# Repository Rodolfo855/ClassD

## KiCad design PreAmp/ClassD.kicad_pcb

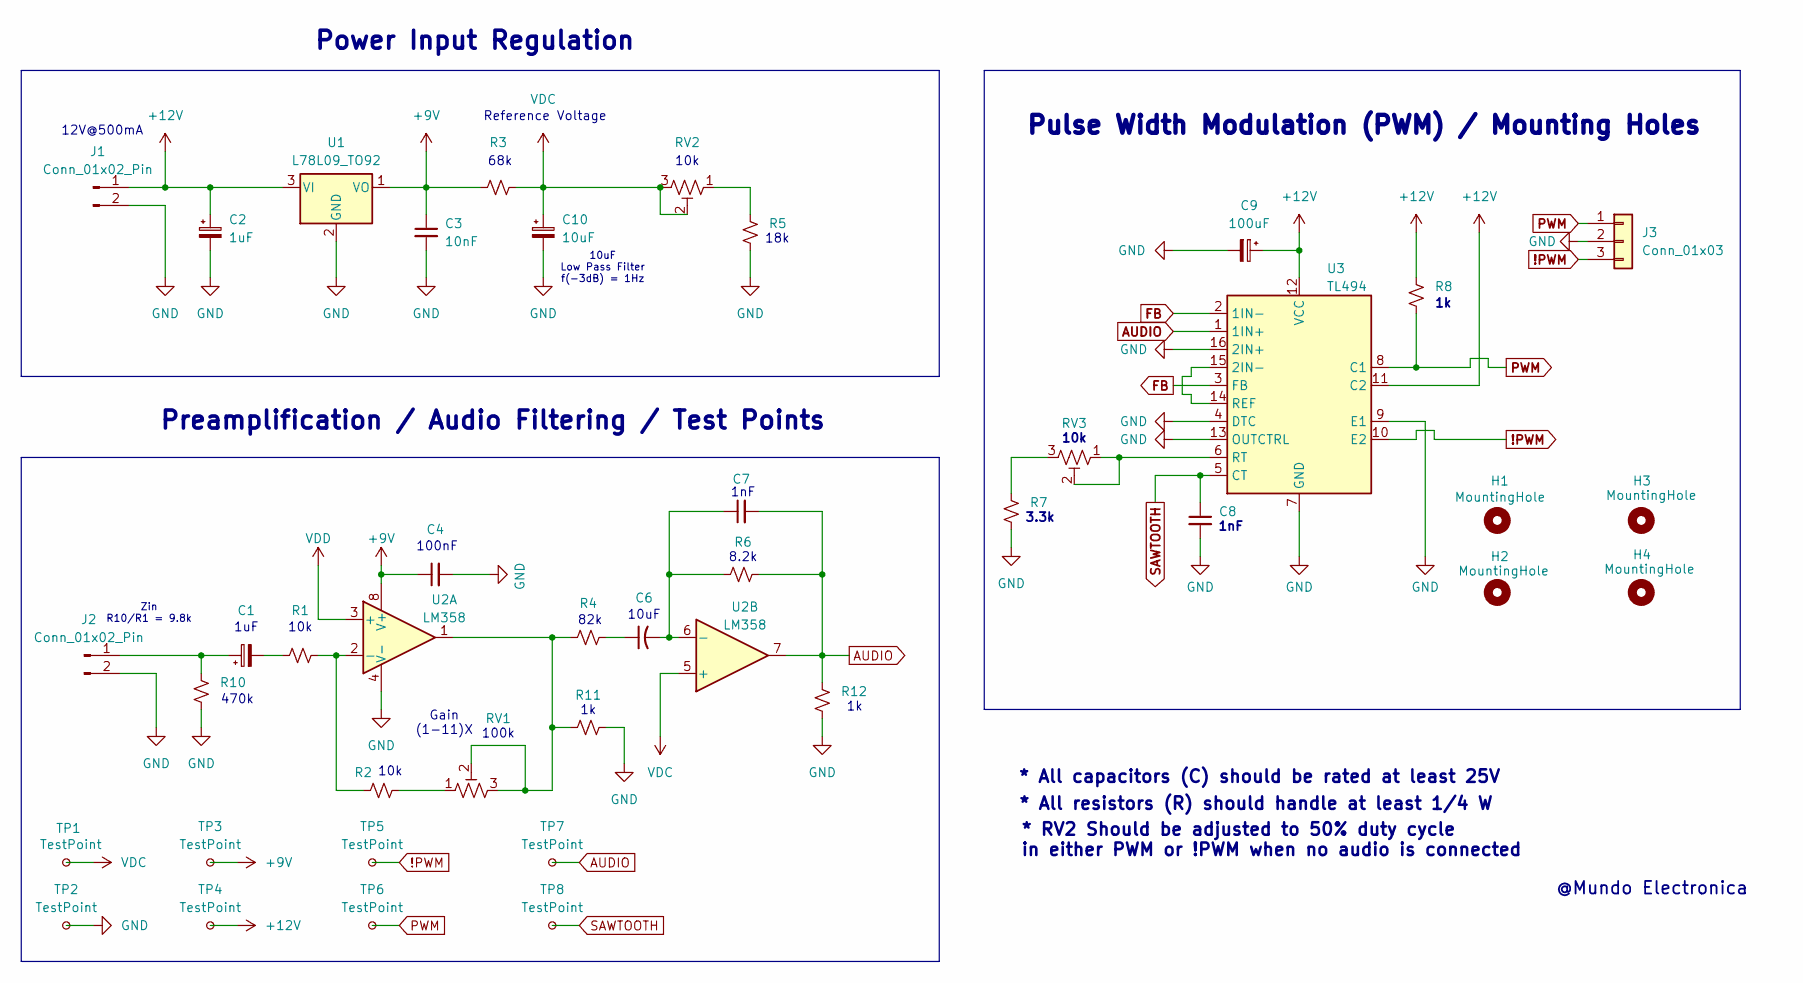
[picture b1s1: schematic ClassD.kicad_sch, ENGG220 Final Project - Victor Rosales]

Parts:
C1: C_Polarized_Small; CP_Radial_D5.0mm_P2.00mm
C2: 1uF; CP_Radial_D5.0mm_P2.00mm
C3: 10nF; C_Disc_D3.8mm_W2.6mm_P2.50mm
C4: C_Small; C_Disc_D5.0mm_W2.5mm_P5.00mm
C6: C_Small_US; CP_Radial_D5.0mm_P2.00mm
C7, C8: C_Small; C_Disc_D3.8mm_W2.6mm_P2.50mm
C9: 100uF; CP_Radial_D8.0mm_P3.50mm
C10: 10uF; CP_Radial_D5.0mm_P2.00mm
H1, H2, H3, H4: MountingHole; MountingHole_3.2mm_M3_Pad_Via
J1: Conn_01x02_Pin; BarrelJack_GCT_DCJ200-10-A_Horizontal
J2: Conn_01x02_Pin; JST_XH_B3B-XH-A_1x03_P2.50mm_Vertical
J3: Conn_01x03; JST_XH_B3B-XH-A_1x03_P2.50mm_Vertical
R1, R2, R3, R4, R5, R6, R7, R8, R10, R11, R12: R_Small_US; R_Axial_DIN0204_L3.6mm_D1.6mm_P7.62mm_Horizontal
RV1, RV2, RV3: R_Potentiometer_Trim_US; Potentiometer_Bourns_3296W_Vertical
TP1, TP2, TP3, TP4, TP5, TP6, TP7, TP8: TestPoint; TestPoint_THTPad_D2.0mm_Drill1.0mm
U1: L78L09_TO92; TO-92_Inline_Wide
U2: LM358; DIP-8_W7.62mm_Socket
U3: TL494; DIP-18_W7.62mm_Socket

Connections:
!PWM: J3.3, TP5.1, U3.10 (E2)
+9V: C3.1, C4.1, R3.1, TP3.1, U1.1 (VO), U2.8 (V+)
+12V: C2.1, C9.1, J1.1, R8.1, TP4.1, U1.3 (VI), U3.11 (C2), U3.12 (VCC)
AUDIO: C7.2, R6.2, R12.1, TP7.1, U2.7, U3.1 (1IN+)
FB: U3.2 (1IN-), U3.3 (FB)
GND: C2.2, C3.2, C4.2, C8.2, C9.2, C10.2, J1.2, J2.2, J3.2, R5.2, R7.2, R10.2, R11.2, R12.2, TP2.1, U1.2 (GND), U2.4 (V-), U3.4 (DTC), U3.7 (GND), U3.9 (E1), U3.13 (OUTCTRL), U3.16 (2IN+)
unnamed: C1.2, R1.1
unnamed: C6.1, R4.2
unnamed: C1.1, J2.1, R10.1
unnamed: R2.2, RV1.1
unnamed: R5.1, RV2.1
unnamed: R7.1, RV3.3
unnamed: R4.1, R11.1, RV1.2, RV1.3, U2.1
unnamed: R1.2, R2.1, U2.2 (-)
unnamed: C6.2, C7.1, R6.1, U2.6 (-)
unnamed: U3.14 (REF), U3.15 (2IN-)
unnamed: RV3.1, RV3.2, U3.6 (RT)
PWM: J3.1, R8.2, TP6.1, U3.8 (C1)
SAWTOOTH: C8.1, TP8.1, U3.5 (CT)
VDC: C10.1, R3.2, RV2.2, RV2.3, TP1.1, U2.5 (+)
VDD: U2.3 (+)

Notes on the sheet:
Pulse Width Modulation (PWM) / Mounting Holes
3.3k
Power Input Regulation
1nF
* All capacitors (C) should be rated at least 25V
100k
Reference Voltage
470k
1uF
10k
10uF Low Pass Filter f(-3dB) = 1Hz
* All resistors (R) should handle at least 1/4 W
@Mundo Electronica
68k
* RV2 Should be adjusted to 50% duty cycle in either PWM or !PWM when no audio is connected
Preamplification / Audio Filtering / Test Points
8.2k
12V@500mA
18k
Zin R10/R1 = 9.8k
82k
Gain (1-11)X
10uF
100nF

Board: 2 copper layers, 41 parts (0 on the bottom side), 20 nets, no tracks yet.

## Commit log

2026-04-29 Init Class D repo
2026-04-30 Added audio input
2026-04-30 Finished Schematic Class D
2026-04-30 Added PDF file for schematic
2026-04-30 init power stage
2026-04-30 init LTSpice animation
2026-05-03 Finished power stage
2026-05-03 Fixed routing
2026-05-03 Created schematic pdf
2026-05-03 Added Speaker Freq Impedence Response Simulation
2026-05-03 Ignored DS files
2026-05-04 Added pfs
2026-05-04 Added PFS's and SS
2026-05-04 Added files to git ignore
2026-05-04 Ignored DS_Store
2026-05-04 Remove DS_Store from tracking
2026-05-04 Renamed pre amp input regulation
2026-05-04 Assigned footprints to all components in Pre Amplification Stage
2026-05-04 Fixed audio jack to 2 pins
2026-05-04 Added shematic for LTSpice simulation
2026-05-04 Added Filter Atenuation Response Simulation
2026-05-05 Added input low pass simulation LTSpice
2026-05-05 Added low pass/high pass filter simulations
2026-05-09 Added screenshots
2026-05-09 Added full fridge simulation LTSpice
2026-05-12 Added pictures, and write-up
2026-05-19 Fixed gain on second op-amp
2026-06-10 Added gerber files
2026-06-25 Fixed R9 and pdf
